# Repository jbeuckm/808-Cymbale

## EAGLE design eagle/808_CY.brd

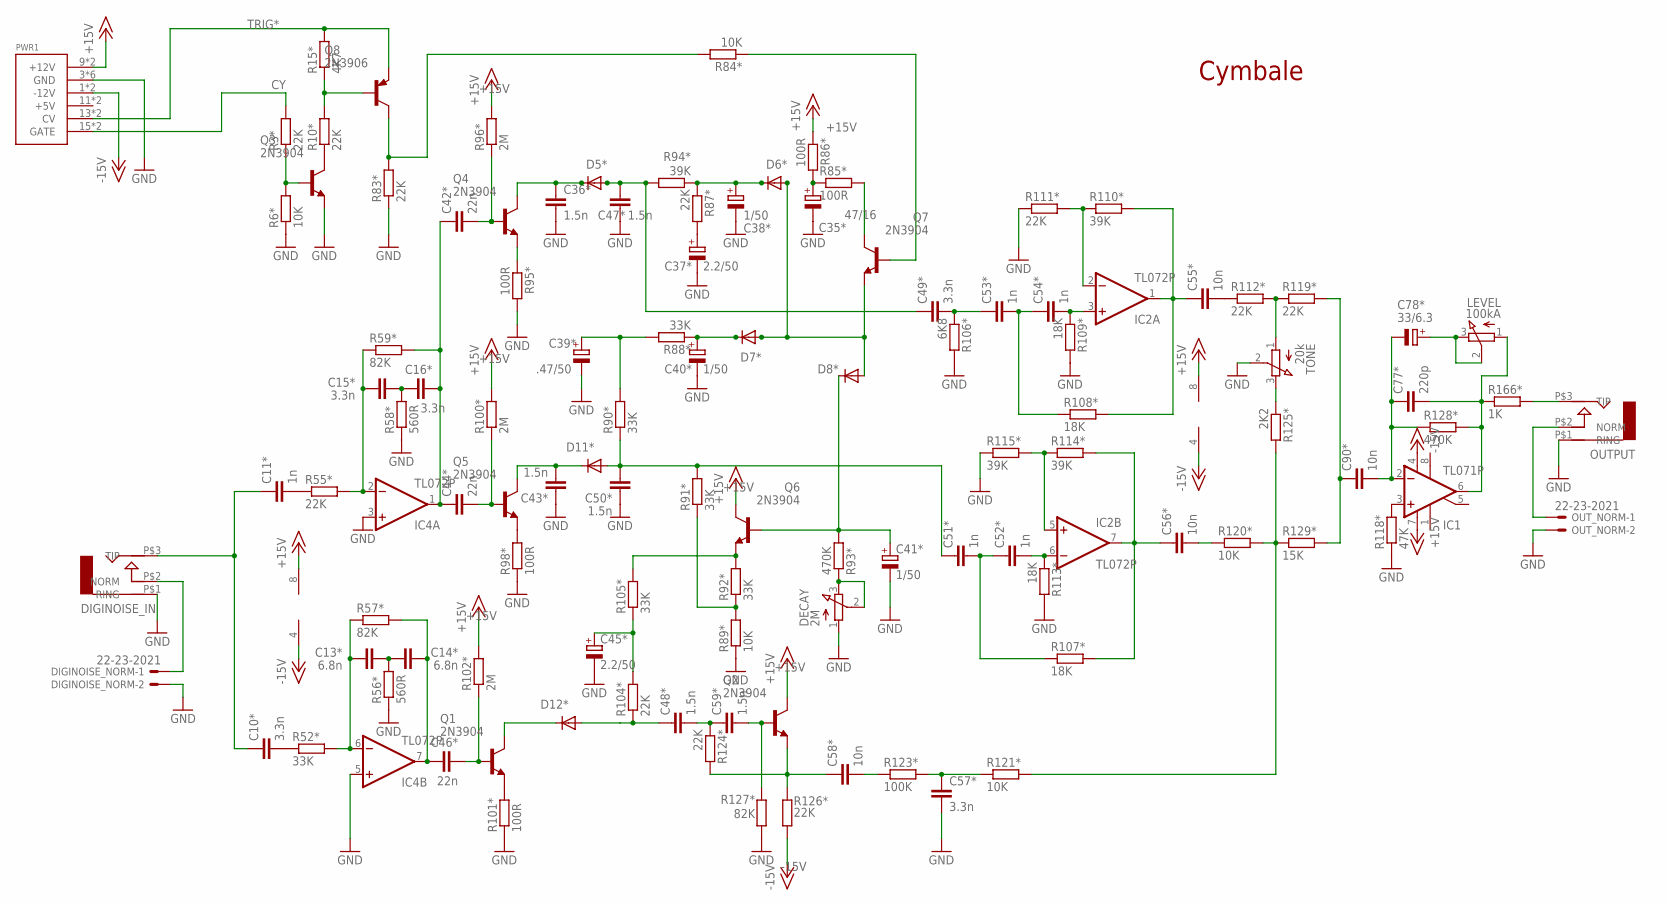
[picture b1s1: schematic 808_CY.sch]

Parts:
C10*, C15*, C16*, C49*, C57*: 3.3n; C035-025X75
C11*, C51*, C52*, C53*, C54*: 1n; C035-025X75
C13*, C14*: 6.8n; C035-030X60
C35*: 47/16; E2,5-5
C36*, C43*, C48*, C50*, C59*: 1.5n; C035-025X75
C37*, C45*: 2.2/50; E2,5-5
C38*, C40*: 1/50; E2,5-5
C39*: .47/50; E2,5-5
C41*: 1/50; E3,5-8
C42*, C44*, C46*: 22n; C050-024X044
C47*: 1.5n; C050-035X075
C55*: 10n; C050-030X075
C56*, C58*, C90*: 10n; C035-025X75
C77*: 220p; C025-025X050
C78*: 33/6.3; E3,5-8
D5*: 1N4148DO35-10; DO35-10
D6*, D7*, D8*, D11*, D12*: 1N4148DO35-7; DO35-7
DECAY: 2M; 3RP/1610N
DIGINOISE_IN: AUDIO-JACK; ERTHENVAR-JACK-90DEG
DIGINOISE_NORM: 22-23-2021
IC1: TL071P; DIL08
IC2, IC4: TL072P; DIL08
LEVEL: 100kA; 3RP/1610N
OUTPUT: AUDIO-JACK; ERTHENVAR-JACK-90DEG
OUT_NORM: 22-23-2021
PWR1: POWER; POWER_16
Q1, Q2, Q3, Q4, Q5, Q6, Q7: 2N3904; TO92
Q8: 2N3906; TO92
R3*, R10*, R83*, R87*, R104*, R112*, R119*, R124*: 22K; 0207/5V
R6*, R120*: 10K; 0207/5V
R15*: 4K7; 0207/5V
R52*, R88*, R90*: 33K; 0207/5V
R55*, R111*, R126*: 22K; 0207/7
R56*: 560R; 0207/5V
R57*, R127*: 82K; 0207/5V
R58*: 560R; 0207/7
R59*: 82K; 0207/2V
R84*, R89*, R121*: 10K; 0207/7
R85*, R86*, R95*, R98*, R101*: 100R; 0207/7
R91*, R92*: 33K; 0207/7
R93*: 470K; 0207/7
R94*, R114*: 39K; 0207/5V
R96*: 2M; 0207/5V
R100*, R102*: 2M; 0207/7
R105*: 33K; 0309/10
R106*: 6K8; 0207/5V
R107*, R108*: 18K; 0207/5V
R109*, R113*: 18K; 0207/7
R110*, R115*: 39K; 0207/7
R118*: 47K; 0207/5V
R123*: 100K; 0207/7
R125*: 2K2; 0207/5V
R128*: 470K; 0207/5V
R129*: 15K; 0207/5V
R166*: 1K; 0207/7
TONE: 20k; 3RP/1610N

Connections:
+15V: IC1.7 (V+), IC2.8 (V+), IC4.8 (V+), PWR1.9 (+12V), PWR1.10 (+12V), Q2.1 (C), Q6.1 (C), R86*.1, R96*.2, R100*.2, R102*.2
-15V: IC1.4 (V-), IC2.4 (V-), IC4.4 (V-), PWR1.1 (-12V), PWR1.2 (-12V), R126*.2
CY: PWR1.15 (GATE), PWR1.16 (GATE), R3*.2
GND: C35*.-, C36*.P$2 (2), C37*.-, C38*.-, C39*.-, C40*.-, C41*.-, C43*.P$1 (1), C45*.-, C47*.2, C50*.P$1 (1), C57*.P$2 (2), DECAY.1 (A), DIGINOISE_IN.P$1 (RING), DIGINOISE_NORM.2, IC4.3 (+IN), IC4.5 (+IN), OUTPUT.P$1 (RING), OUT_NORM.2, PWR1.3 (GND), PWR1.4 (GND), PWR1.5 (GND), PWR1.6 (GND), PWR1.7 (GND), PWR1.8 (GND), Q3.3 (E), R6*.1, R56*.1, R58*.1, R83*.1, R89*.1, R95*.2, R98*.1, R101*.1, R106*.2, R109*.2, R111*.1, R113*.2, R115*.1, R118*.1, R127*.2, TONE.2 (S)
LT_LC_OUT1: C10*.P$1 (1), C11*.P$1 (1), DIGINOISE_IN.P$3 (TIP)
unnamed: Q5.3 (E), R98*.2
unnamed: Q1.3 (E), R101*.2
unnamed: Q3.1 (C), R10*.1
unnamed: IC1.3 (+IN), R118*.2
unnamed: OUTPUT.P$2 (NORM), OUT_NORM.1
unnamed: DIGINOISE_IN.P$2 (NORM), DIGINOISE_NORM.1
unnamed: OUTPUT.P$3 (TIP), R166*.2
unnamed: C78*.+, LEVEL.2 (S), LEVEL.3 (E)
unnamed: C58*.P$1 (1), Q2.3 (E), R124*.2, R126*.1
unnamed: DECAY.2 (S), DECAY.3 (E), R93*.1
unnamed: Q4.3 (E), R95*.1
unnamed: C50*.P$2 (2), C51*.P$1 (1), D11*.A, R90*.1, R91*.2
unnamed: C11*.P$2 (2), R55*.1
unnamed: C15*.P$1 (1), IC4.2 (-IN), R55*.2, R59*.1
unnamed: C44*.2, Q5.2 (B), R100*.1
unnamed: C43*.P$2 (2), D11*.C, Q5.1 (C)
unnamed: C39*.+, R88*.2, R90*.2
unnamed: C10*.P$2 (2), R52*.1
unnamed: C13*.P$1 (1), IC4.6 (-IN), R52*.2, R57*.1
unnamed: C14*.P$2 (2), C46*.1, IC4.7 (OUT), R57*.2
unnamed: C46*.2, Q1.2 (B), R102*.1
unnamed: D12*.C, Q1.1 (C)
unnamed: C48*.P$1 (1), D12*.A, R104*.1
unnamed: C40*.+, D7*.C, R88*.1
unnamed: C35*.+, R85*.1, R86*.2
unnamed: Q7.1 (C), R85*.2
unnamed: D6*.A, D7*.A, D8*.A, Q7.3 (E)
unnamed: Q7.2 (B), R84*.1
unnamed: Q8.1 (C), R83*.2, R84*.2
unnamed: Q8.2 (B), R10*.2, R15*.1
unnamed: Q3.2 (B), R3*.1, R6*.2
unnamed: C36*.P$1 (1), D5*.C, Q4.1 (C)
unnamed: C47*.1, C49*.P$1 (1), D5*.A, R94*.2
unnamed: C42*.2, Q4.2 (B), R96*.1
unnamed: C37*.+, R87*.2
unnamed: Q6.3 (E), R92*.2, R105*.2
unnamed: R89*.2, R91*.1, R92*.1
unnamed: C41*.+, D8*.C, Q6.2 (B), R93*.2
unnamed: C49*.P$2 (2), C53*.P$1 (1), R106*.1
unnamed: C54*.P$2 (2), IC2.3 (+IN), R109*.1
unnamed: R112*.2, R119*.1, TONE.1 (A)
unnamed: C55*.1, IC2.1 (OUT), R108*.2, R110*.2
unnamed: C53*.P$2 (2), C54*.P$1 (1), R108*.1
unnamed: IC2.2 (-IN), R110*.1, R111*.2
unnamed: C55*.2, R112*.1
unnamed: R125*.1, TONE.3 (E)
unnamed: C52*.P$2 (2), IC2.6 (-IN), R113*.1
unnamed: C56*.P$1 (1), IC2.7 (OUT), R107*.2, R114*.2
unnamed: C51*.P$2 (2), C52*.P$1 (1), R107*.1
unnamed: IC2.5 (+IN), R114*.1, R115*.2
unnamed: C77*.1, C78*.-, C90*.P$2 (2), IC1.2 (-IN), R128*.1
unnamed: C77*.2, IC1.6 (OUT), LEVEL.1 (A), R128*.2, R166*.1
unnamed: C56*.P$2 (2), R120*.1
unnamed: R120*.2, R121*.2, R125*.2, R129*.1
unnamed: C90*.P$1 (1), R119*.2, R129*.2
unnamed: C48*.P$2 (2), C59*.P$1 (1), R124*.1
unnamed: C59*.P$2 (2), Q2.2 (B), R127*.1
unnamed: C58*.P$2 (2), R123*.1
unnamed: C57*.P$1 (1), R121*.1, R123*.2
unnamed: C15*.P$2 (2), C16*.P$1 (1), R58*.2
unnamed: C13*.P$2 (2), C14*.P$1 (1), R56*.2
unnamed: C45*.+, R104*.2, R105*.1
unnamed: C38*.+, D6*.C, R87*.1, R94*.1
TO_HH: C16*.P$2 (2), C42*.1, C44*.1, IC4.1 (OUT), R59*.2
TRIG*: PWR1.13 (CV), PWR1.14 (CV), Q8.3 (E), R15*.2

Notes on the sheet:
Cymbale

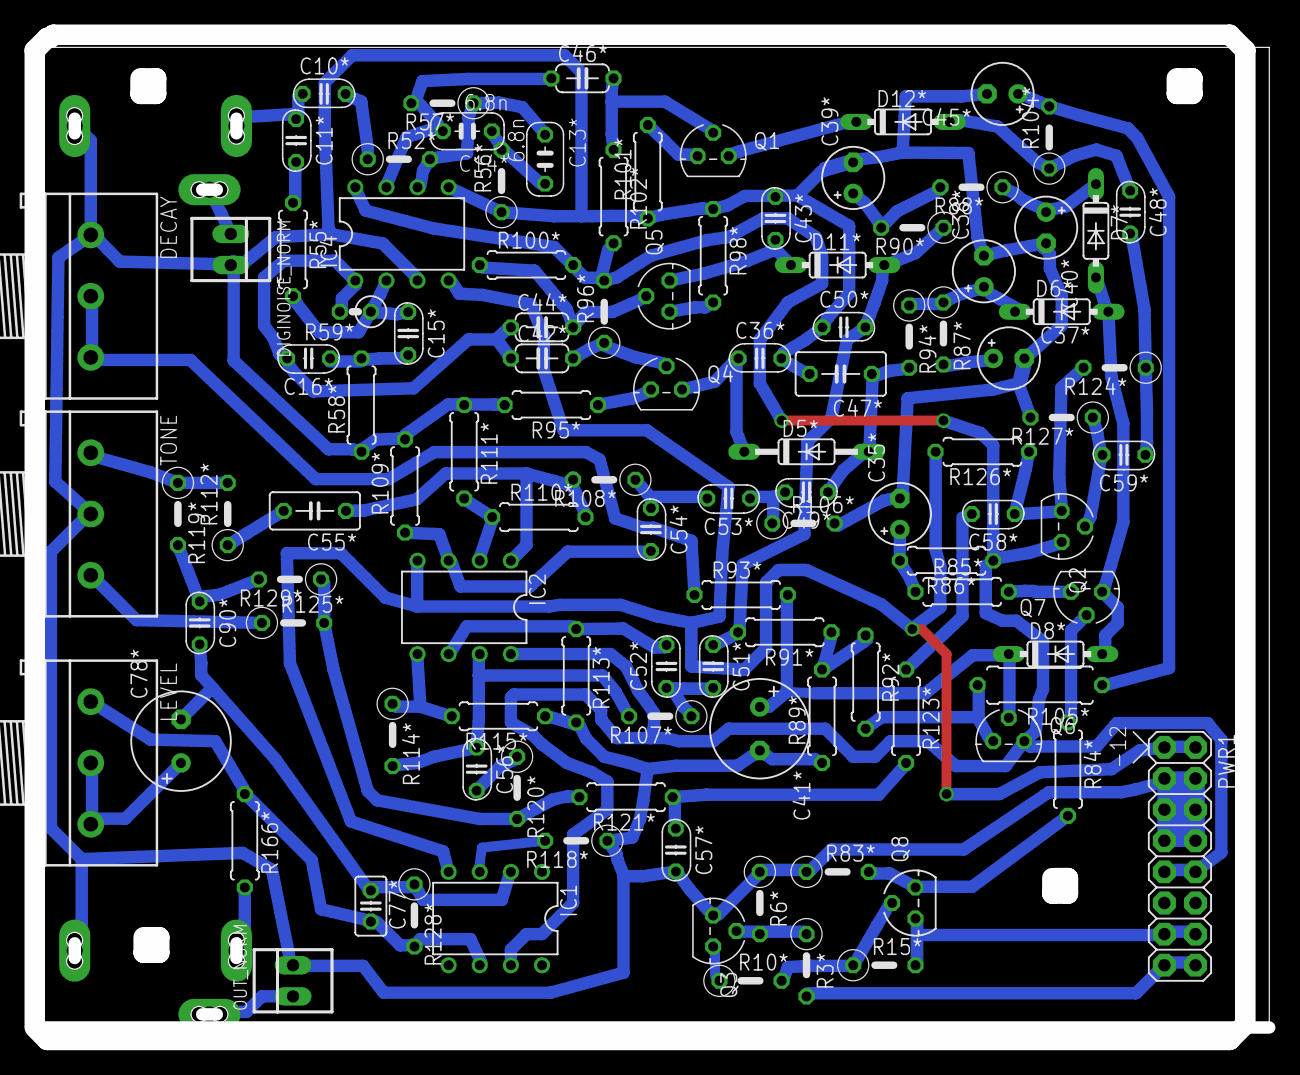
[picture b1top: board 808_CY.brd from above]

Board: 2 copper layers, 100.8 x 82.0 mm, 111 parts (0 on the bottom side), 70 nets.

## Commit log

2016-04-19 subbed opamps
2016-04-19 moved diginoise off-board
2016-04-19 corrected bad connection on 071s
2016-04-19 starting the layout
2016-04-20 consolidated double 1m resistors
2016-04-20 third of the parts on
2016-04-20 parts on the board
2016-04-20 90 pct routed
2016-04-20 tweaks
2016-04-21 trying a smaller width
2016-04-21 finishing routes manually
2016-04-22 more routes
2016-04-22 ar 94pct with 072 replacing two 071
2016-04-23 finishing manually with two 072
2016-04-23 more manual routes
2016-04-23 routed and tweaked
2016-04-23 checked schemo and generated gcode
2016-04-24 will try gcode
2016-04-25 tweaks aftrer working build
